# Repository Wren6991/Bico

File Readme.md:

# Bico

A Pico-shaped board with two RP2040s and two USB sockets. One of the RP2040s does everything you would normally expect from a Pico, while the other provides a debug probe interface for the main RP2040. SWD and UART are connected directly between the two RP2040s on-board, so there are no flying wires required.

The board can be powered from either USB socket. One socket provides USB access to the main RP2040, and the other one provides debug and serial access via the probe RP2040. You can plug in both at the same time, though ideally on the same machine as this will short the grounds and shields of the two USB cables together.

Both RP2040s have BOOTSEL buttons for loading firmware over USB. The main RP2040 also has a reset button.

Schematic is [here](board/bico.pdf) (PDF link)

License: CC0

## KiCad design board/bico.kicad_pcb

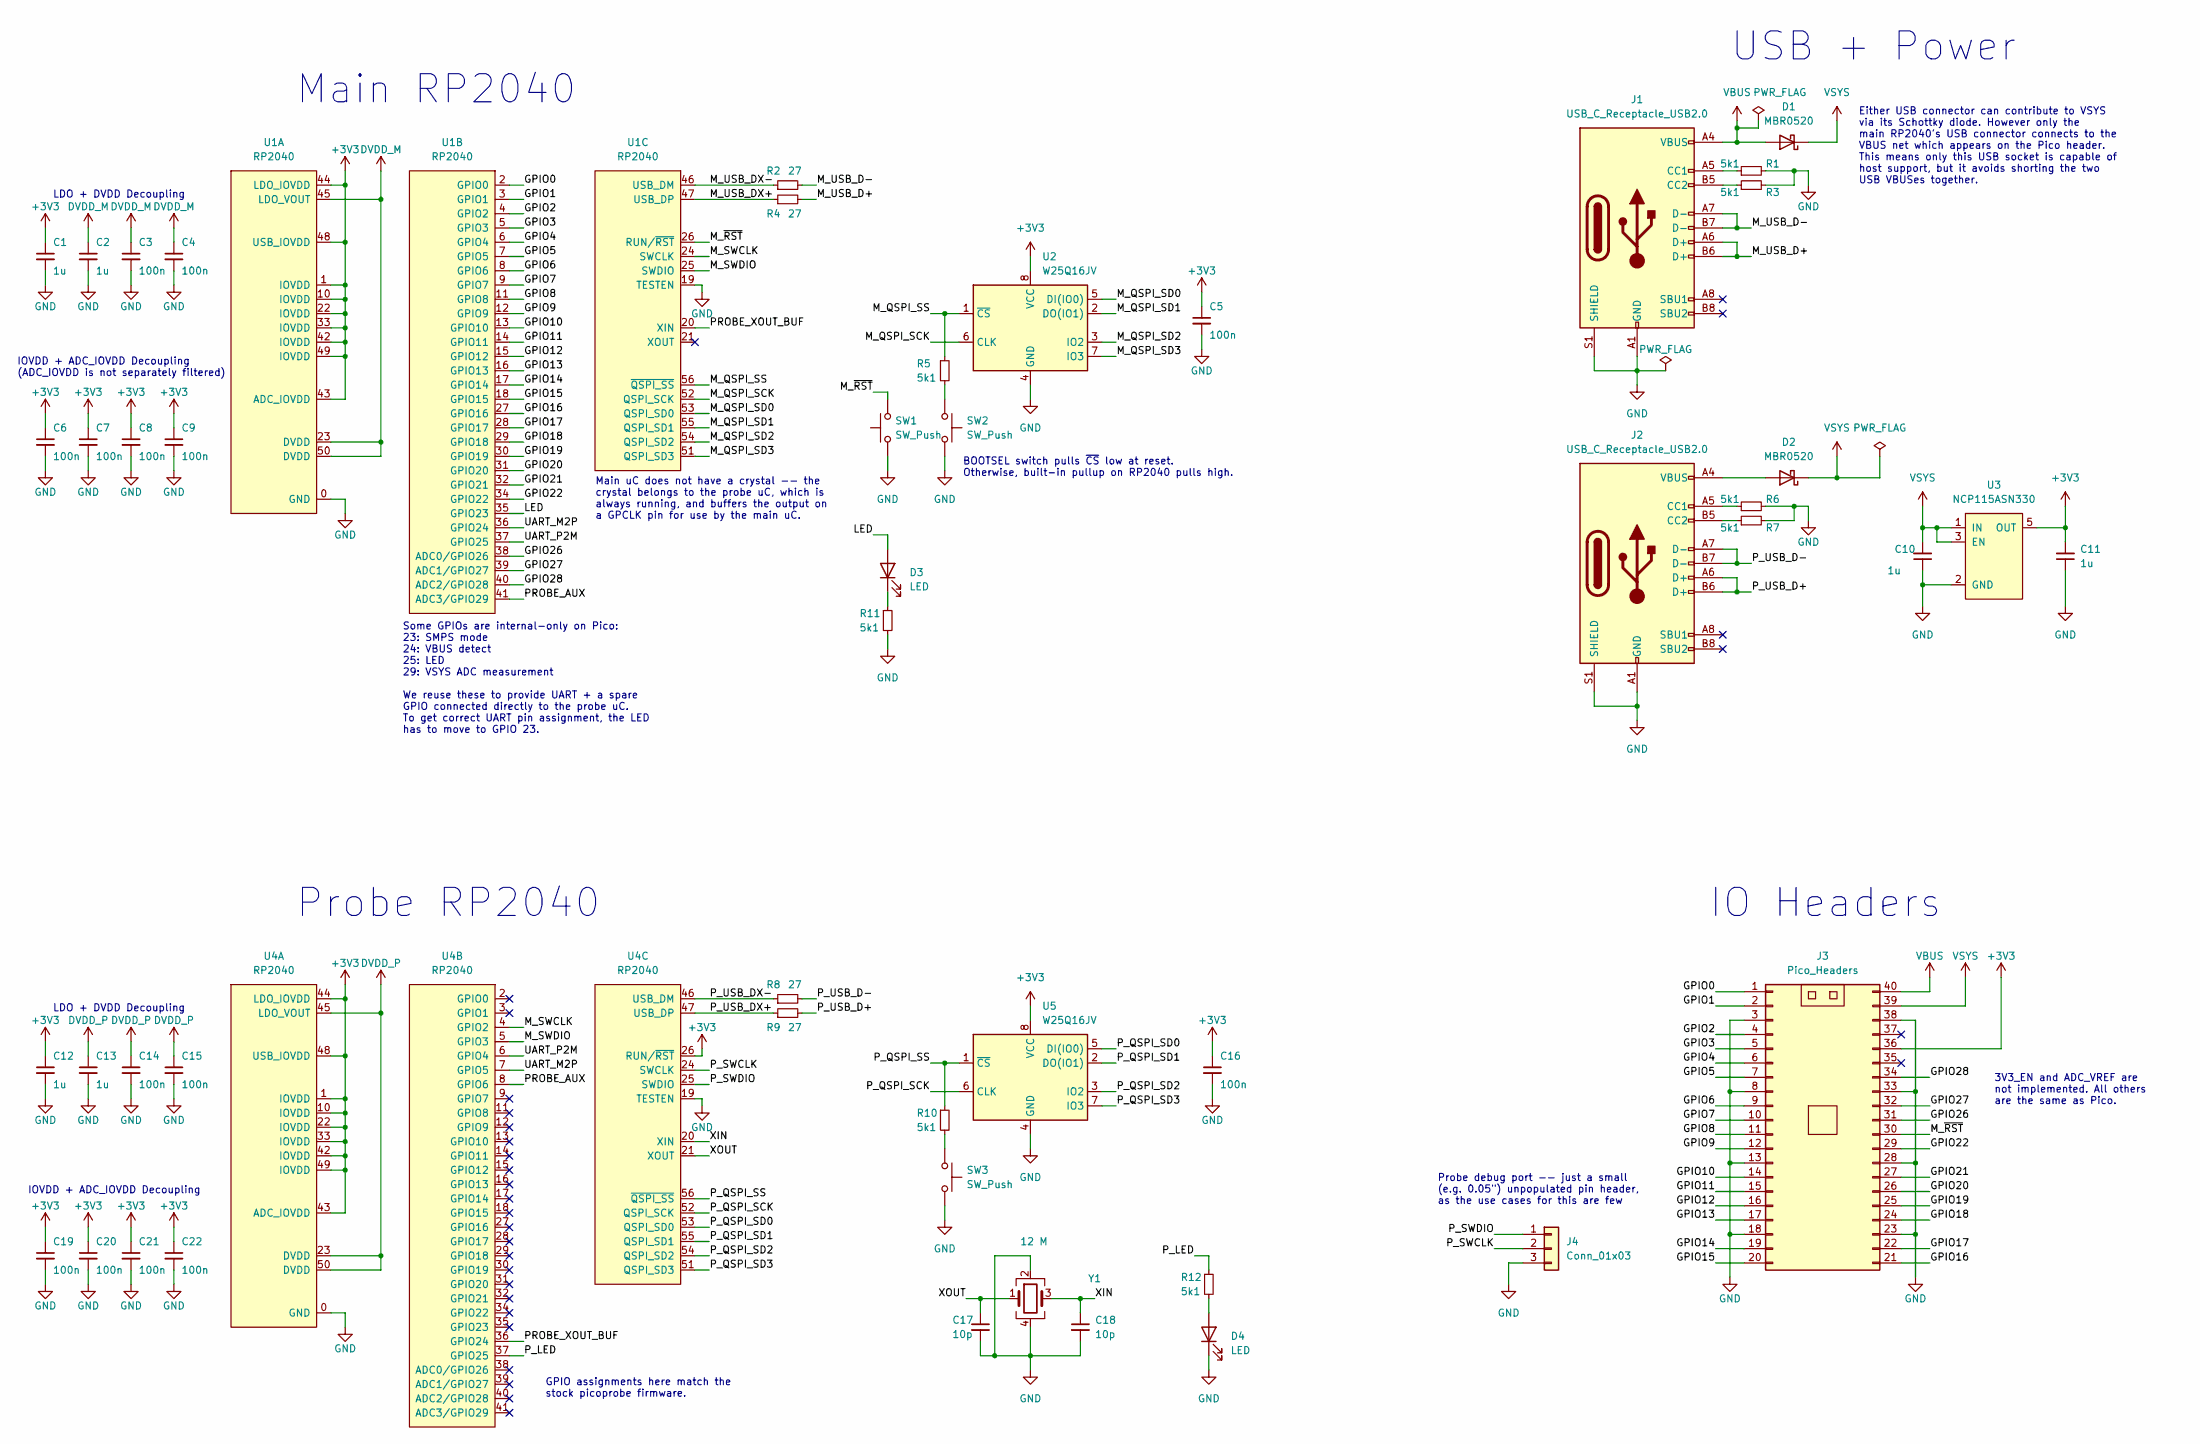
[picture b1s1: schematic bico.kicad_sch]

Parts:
C1, C2, C10, C11, C12, C13: 1u; C_0402_1005Metric
C3, C4, C5, C6, C7, C8, C9, C14, C15, C16, C19, C20, C21, C22: 100n; C_0402_1005Metric
C17, C18: 10p; C_0402_1005Metric
D1, D2: MBR0520; D_SOD-123
D3, D4: LED; LED_0603_1608Metric
J1, J2: USB_C_Receptacle_USB2.0; USB_C_Receptacle_GCT_USB4105-xx-A_16P_TopMnt_Horizontal
J3: Pico_Headers
J4: Conn_01x03; PinHeader_1x03_P1.00mm_Vertical
R1, R3, R5, R6, R7, R10, R11, R12: 5k1; R_0402_1005Metric
R2, R4, R8, R9: 27; R_0402_1005Metric
SW1, SW2, SW3: SW_Push; SW_SPST_PTS815
U1, U4: RP2040; QFN-56_EP_7x7_Pitch0.4mm
U2, U5: W25Q16JV; DFN-8-3x2mm-Winbond
U3: NCP115ASN330; SOT-23-5_HandSoldering
Y1: 12 M; Crystal_SMD_3225-4Pin_3.2x2.5mm

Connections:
+3V3: C1.1, C5.1, C6.1, C7.1, C8.1, C9.1, C11.2, C12.1, C16.1, C19.1, C20.1, C21.1, C22.1, J3.36, U1.1 (IOVDD), U1.10 (IOVDD), U1.22 (IOVDD), U1.33 (IOVDD), U1.42 (IOVDD), U1.43 (ADC_IOVDD), U1.44 (LDO_IOVDD), U1.48 (USB_IOVDD), U1.49 (IOVDD), U2.8 (VCC), U3.5 (OUT), U4.1 (IOVDD), U4.10 (IOVDD), U4.22 (IOVDD), U4.26 (RUN/~RST), U4.33 (IOVDD), U4.42 (IOVDD), U4.43 (ADC_IOVDD), U4.44 (LDO_IOVDD), U4.48 (USB_IOVDD), U4.49 (IOVDD), U5.8 (VCC)
/GPIO0: J3.1, U1.2 (GPIO0)
/GPIO1: J3.2, U1.3 (GPIO1)
/GPIO2: J3.4, U1.4 (GPIO2)
/GPIO3: J3.5, U1.5 (GPIO3)
/GPIO4: J3.6, U1.6 (GPIO4)
/GPIO5: J3.7, U1.7 (GPIO5)
/GPIO6: J3.9, U1.8 (GPIO6)
/GPIO7: J3.10, U1.9 (GPIO7)
/GPIO8: J3.11, U1.11 (GPIO8)
/GPIO9: J3.12, U1.12 (GPIO9)
/GPIO10: J3.14, U1.13 (GPIO10)
/GPIO11: J3.15, U1.14 (GPIO11)
/GPIO12: J3.16, U1.15 (GPIO12)
/GPIO13: J3.17, U1.16 (GPIO13)
/GPIO14: J3.19, U1.17 (GPIO14)
/GPIO15: J3.20, U1.18 (GPIO15)
/GPIO16: J3.21, U1.27 (GPIO16)
/GPIO17: J3.22, U1.28 (GPIO17)
/GPIO18: J3.24, U1.29 (GPIO18)
/GPIO19: J3.25, U1.30 (GPIO19)
/GPIO20: J3.26, U1.31 (GPIO20)
/GPIO21: J3.27, U1.32 (GPIO21)
/GPIO22: J3.29, U1.34 (GPIO22)
/GPIO26: J3.31, U1.38 (ADC0/GPIO26)
/GPIO27: J3.32, U1.39 (ADC1/GPIO27)
/GPIO28: J3.34, U1.40 (ADC2/GPIO28)
/LED: D3.2 (A), U1.35 (GPIO23)
/M_QSPI_SCK: U1.52 (QSPI_SCK), U2.6 (CLK)
/M_QSPI_SD0: U1.53 (QSPI_SD0), U2.5 (DI(IO0))
/M_QSPI_SD1: U1.55 (QSPI_SD1), U2.2 (DO(IO1))
/M_QSPI_SD2: U1.54 (QSPI_SD2), U2.3 (IO2)
/M_QSPI_SD3: U1.51 (QSPI_SD3), U2.7 (IO3)
/M_QSPI_SS: R5.1, U1.56 (~QSPI_SS), U2.1 (~CS)
/M_SWCLK: U1.24 (SWCLK), U4.4 (GPIO2)
/M_SWDIO: U1.25 (SWDIO), U4.5 (GPIO3)
/M_USB_D+: J1.A6 (D+), J1.B6 (D+), R4.2
/M_USB_D-: J1.A7 (D-), J1.B7 (D-), R2.2
/M_USB_DX+: R4.1, U1.47 (USB_DP)
/M_USB_DX-: R2.1, U1.46 (USB_DM)
/M_~RST: J3.30, SW1.1, U1.26 (RUN/~RST)
/PROBE_AUX: U1.41 (ADC3/GPIO29), U4.8 (GPIO6)
/PROBE_XOUT_BUF: U1.20 (XIN), U4.36 (GPIO24)
/P_LED: R12.1, U4.37 (GPIO25)
/P_QSPI_SCK: U4.52 (QSPI_SCK), U5.6 (CLK)
/P_QSPI_SD0: U4.53 (QSPI_SD0), U5.5 (DI(IO0))
/P_QSPI_SD1: U4.55 (QSPI_SD1), U5.2 (DO(IO1))
/P_QSPI_SD2: U4.54 (QSPI_SD2), U5.3 (IO2)
/P_QSPI_SD3: U4.51 (QSPI_SD3), U5.7 (IO3)
/P_QSPI_SS: R10.1, U4.56 (~QSPI_SS), U5.1 (~CS)
/P_SWCLK: J4.2, U4.24 (SWCLK)
/P_SWDIO: J4.1, U4.25 (SWDIO)
/P_USB_D+: J2.A6 (D+), J2.B6 (D+), R9.2
/P_USB_D-: J2.A7 (D-), J2.B7 (D-), R8.2
/P_USB_DX+: R9.1, U4.47 (USB_DP)
/P_USB_DX-: R8.1, U4.46 (USB_DM)
/UART_M2P: U1.36 (GPIO24), U4.7 (GPIO5)
/UART_P2M: U1.37 (GPIO25), U4.6 (GPIO4)
/XIN: C18.1, U4.20 (XIN), Y1.3
/XOUT: C17.1, U4.21 (XOUT), Y1.1
DVDD_M: C2.1, C3.1, C4.1, U1.23 (DVDD), U1.45 (LDO_VOUT), U1.50 (DVDD)
DVDD_P: C13.1, C14.1, C15.1, U4.23 (DVDD), U4.45 (LDO_VOUT), U4.50 (DVDD)
GND: C1.2, C2.2, C3.2, C4.2, C5.2, C6.2, C7.2, C8.2, C9.2, C10.1, C11.1, C12.2, C13.2, C14.2, C15.2, C16.2, C17.2, C18.2, C19.2, C20.2, C21.2, C22.2, D4.1 (K), J1.A1 (GND), J1.A12 (GND), J1.B1 (GND), J1.B12 (GND), J1.S1 (SHIELD), J2.A1 (GND), J2.A12 (GND), J2.B1 (GND), J2.B12 (GND), J2.S1 (SHIELD), J3.3, J3.8, J3.13, J3.18, J3.23, J3.28, J3.33, J3.38, J4.3, R1.2, R3.2, R6.2, R7.2, R11.2, SW1.2, SW2.1, SW3.2, U1.0 (GND), U1.19 (TESTEN), U2.4 (GND), U3.2 (GND), U4.0 (GND), U4.19 (TESTEN), U5.4 (GND), Y1.2, Y1.4
unnamed: D2.2 (A), J2.A4 (VBUS), J2.A9 (VBUS), J2.B4 (VBUS), J2.B9 (VBUS)
unnamed: D3.1 (K), R11.1
unnamed: J1.A5 (CC1), R1.1
unnamed: J1.B5 (CC2), R3.1
unnamed: J2.A5 (CC1), R6.1
unnamed: J2.B5 (CC2), R7.1
unnamed: R5.2, SW2.2
unnamed: R10.2, SW3.1
unnamed: D4.2 (A), R12.2
VBUS: D1.2 (A), J1.A4 (VBUS), J1.A9 (VBUS), J1.B4 (VBUS), J1.B9 (VBUS), J3.40
VSYS: C10.2, D1.1 (K), D2.1 (K), J3.39, U3.1 (IN), U3.3 (EN)

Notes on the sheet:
Main uC does not have a crystal -- the crystal belongs to the probe uC, which is always running, and buffers the output on a GPCLK pin for use by the main uC.
IOVDD + ADC_IOVDD Decoupling (ADC_IOVDD is not separately filtered)
LDO + DVDD Decoupling
3V3_EN and ADC_VREF are not implemented. All others are the same as Pico.
USB + Power
Probe RP2040
Probe debug port -- just a small (e.g. 0.05") unpopulated pin header, as the use cases for this are few
Some GPIOs are internal-only on Pico: 23: SMPS mode 24: VBUS detect 25: LED 29: VSYS ADC measurement We reuse these to provide UART + a spare GPIO connected directly to the probe uC. To get correct UART pin assignment, the LED has to move to GPIO 23.
GPIO assignments here match the stock picoprobe firmware.
IO Headers
Either USB connector can contribute to VSYS via its Schottky diode. However only the main RP2040's USB connector connects to the VBUS net which appears on the Pico header. This means only this USB socket is capable of host support, but it avoids shorting the two USB VBUSes together.
IOVDD + ADC_IOVDD Decoupling
BOOTSEL switch pulls ~{CS} low at reset. Otherwise, built-in pullup on RP2040 pulls high.
Main RP2040

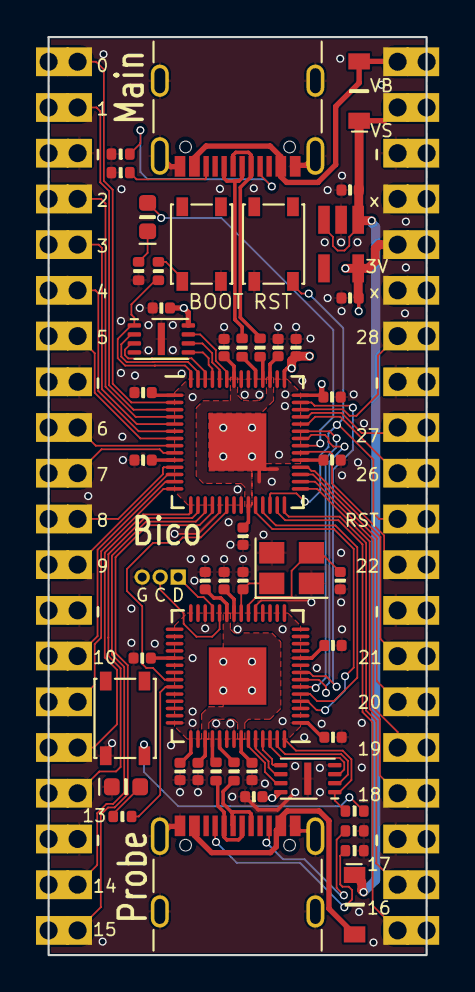
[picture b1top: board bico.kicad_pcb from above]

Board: 4 copper layers, 21.0 x 51.0 mm, 51 parts (0 on the bottom side), 74 nets.

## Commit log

2023-04-23 Initial commit, very rough schematic sketched in
2023-04-23 ERC clean. Split RP2040 DVDDs, and add LEDs and probe debug header
2023-04-23 Assign footprints
2023-04-23 Rough initial placement
2023-04-25 Start routing
2023-04-25 Fully routed
2023-04-25 DRC clean, for now
2023-04-25 Tidy up grounding etc
2023-04-25 Label all pins in silkscreen
2023-04-25 Add github link and silk text to board underside
2023-04-25 Add JLC silk text
2023-04-26 Add generated files and readme
2023-04-26 Create LICENSE
2023-04-26 Tweak readme text
